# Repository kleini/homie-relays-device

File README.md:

# Relays device for controlling arbitrary loads

## Concept

ESP8266 based controller using Homie and a I/O Extender to control 16 relays. Everything should fit in a DIN Rail Standard Height Module Box.

## Hardware

 * ESP8266 12e module
 * I²C I/O Extender MCP23016 (16 GPIOs)
 * self designed board fitting into DIN Rail Standard Height Module Box (see hardware branch)
 * 230V power supply

I²C device address configured to 0x20.

DCDC converter from 12V down to 3.3V running ESP8266 and MCP23016. Some driver chip will be used to drive the relay coils.

Every output will have its own indicator LED.

### MCP23016

This chip is able to drive a LED directly on the high output.

### Lessons learned

#### PCF8575

The PCF8575 has only a very low continuous output high current of -4mA. This allows possibly to light up a low current LED but not much more. Will drop the use of this chip and use something with higher output high current.

## Case

Everything should fit in a DIN Rail Standard Module Box like the following

The design of the printed circuit board will finally show, how much relays I can fit in which box. Current design goal is to have a 3 module wide box. If I can not fit 16 230V 5A relays switches onto the PCB in this box,
I will take a wider box.

The box can carry up to 3 PCBs. I will use only 2, a large one in the bottom for power supply and relays switches and a smaller one in the top for ESP8266, indicator LEDs and I/O expander.

## Compiling

Software will be based on latest homie-esp8266 development cycle.

Extended/modified libraries are necessary.

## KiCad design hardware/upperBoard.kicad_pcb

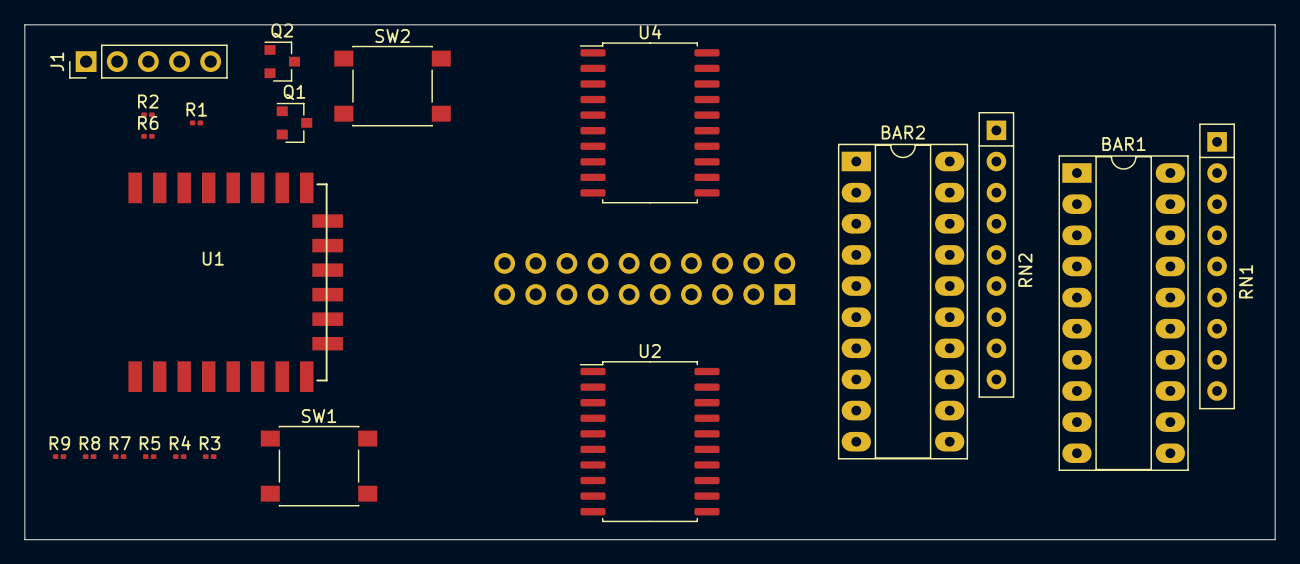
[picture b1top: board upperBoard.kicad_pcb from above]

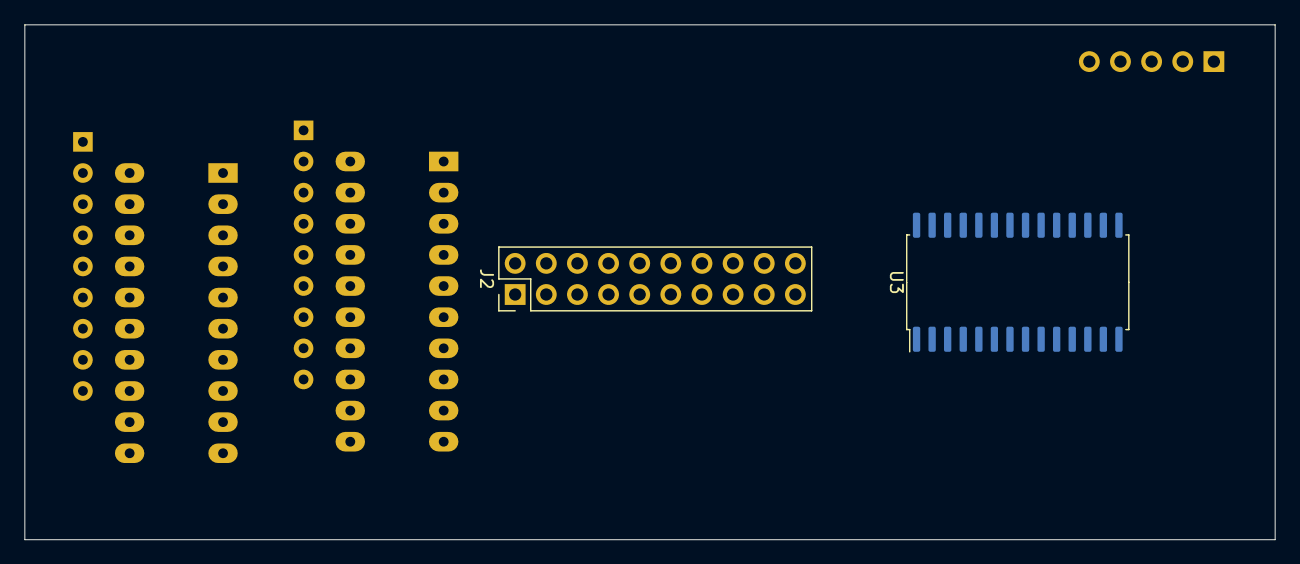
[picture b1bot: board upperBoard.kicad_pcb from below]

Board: 2 copper layers, 102.0 x 42.0 mm, 23 parts (2 on the bottom side), 64 nets, no tracks yet.

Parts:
BAR1, BAR2: HDSP-4830_2; DIP-20_W7.62mm_Socket_LongPads
J1: Program interface; PinHeader_1x05_P2.54mm_Vertical
J2: Conn_02x10_Odd_Even; PinHeader_2x10_P2.54mm_Vertical
Q1, Q2: MMBT3904; SOT-23
R1, R2, R3, R4, R6, R7, R8, R9: 10K; R_0201_0603Metric
R5: 4.7K; R_0201_0603Metric
RN1: 150; R_Array_SIP9
RN2: R_Network08; R_Array_SIP9
SW1: Reset; SW_Push_1P1T_NO_6x6mm_H9.5mm
SW2: Prog; SW_Push_1P1T_NO_6x6mm_H9.5mm
U1: ESP-12F; ESP-12E_SMD
U2, U4: A2982; SOIC-20W_7.5x12.8mm_P1.27mm
U3: MCP23017_SO; SOIC-28W_7.5x17.9mm_P1.27mm

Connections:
/01: J2.15, U2.20
/02: J2.13, U2.19
/03: J2.11, U2.18
/3.3V: J2.17, R1.1, R2.1, R6.1, R7.1, R8.1, R9.1, U1.8, U3.9
/04: J2.9, U2.17
/05: J2.7, U2.16
/06: J2.5, U2.15
/07: J2.3, U2.14
/08: J2.1, U2.13
/09: J2.2, U4.20
/10: J2.4, U4.19
/11: J2.6, U4.18
/12: J2.8, U4.17
/12V: J2.19, U2.9, U4.9
/13: J2.10, U4.16
/14: J2.12, U4.15
/15: J2.14, U4.14
/16: J2.16, U4.13
/DTR: J1.3, Q2.2, R3.1
/GND: J1.5, J2.18, J2.20, R5.2, RN1.1, RN2.1, SW1.1, SW2.2, U1.9, U2.12, U3.10, U3.15, U3.16, U3.17, U4.12
/RTS: J1.4, Q1.2, R4.1
/RXD: J1.1, U1.16
/TXD: J1.2, U1.15
unnamed: BAR1.1, U2.1, U3.21
unnamed: BAR1.2, U2.2, U3.22
unnamed: BAR1.3, U2.3, U3.23
unnamed: BAR1.4, U2.4, U3.24
unnamed: BAR1.5, U2.5, U3.25
unnamed: BAR1.6, U2.6, U3.26
unnamed: BAR1.7, U2.7, U3.27
unnamed: BAR1.8, U2.8, U3.28
unnamed: BAR1.13, RN1.9
unnamed: BAR1.14, RN1.8
unnamed: BAR1.15, RN1.7
unnamed: BAR1.16, RN1.6
unnamed: BAR1.17, RN1.5
unnamed: BAR1.18, RN1.4
unnamed: BAR1.19, RN1.3
unnamed: BAR1.20, RN1.2
unnamed: BAR2.1, U3.1, U4.1
unnamed: BAR2.2, U3.2, U4.2
unnamed: BAR2.3, U3.3, U4.3
unnamed: BAR2.4, U3.4, U4.4
unnamed: BAR2.5, U3.5, U4.5
unnamed: BAR2.6, U3.6, U4.6
unnamed: BAR2.7, U3.7, U4.7
unnamed: BAR2.8, U3.8, U4.8
unnamed: BAR2.13, RN2.9
unnamed: BAR2.14, RN2.8
unnamed: BAR2.15, RN2.7
unnamed: BAR2.16, RN2.6
unnamed: BAR2.17, RN2.5
unnamed: BAR2.18, RN2.4
unnamed: BAR2.19, RN2.3
unnamed: BAR2.20, RN2.2
unnamed: Q1.1, R3.2
unnamed: Q1.3, R1.2, SW1.2, U1.1, U3.18
unnamed: Q2.1, R4.2
unnamed: Q2.3, R6.2, SW2.1, U1.12
unnamed: R2.2, U1.3
unnamed: R5.1, U1.10
unnamed: R7.2, U1.14, U3.12
unnamed: R8.2, U1.13, U3.13
unnamed: R9.2, U1.11

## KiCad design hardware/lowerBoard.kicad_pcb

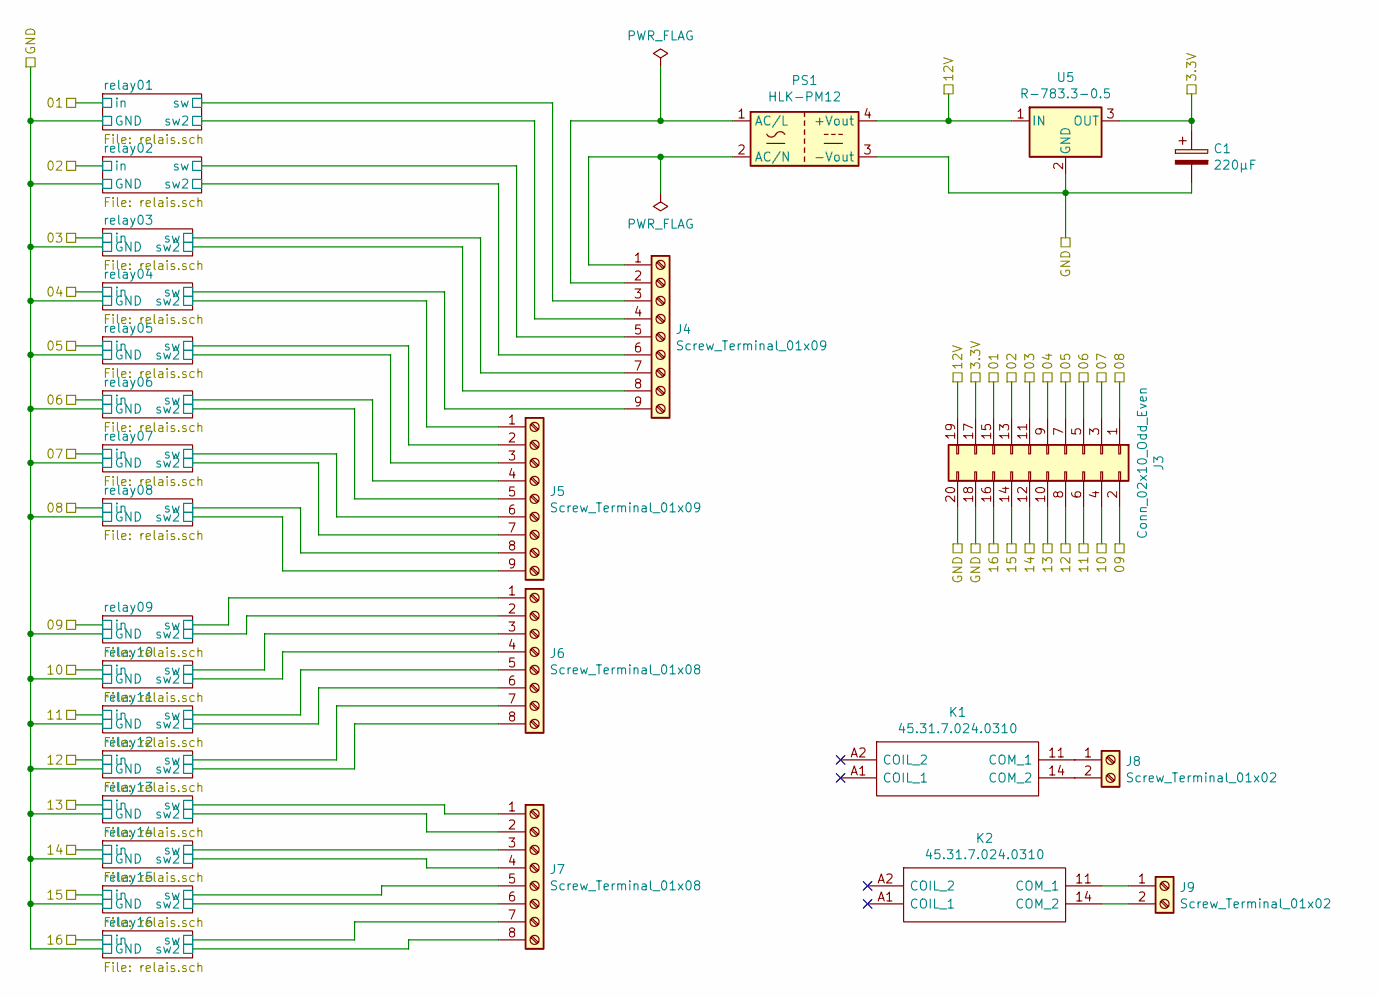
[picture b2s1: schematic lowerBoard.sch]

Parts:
C1: 220µF; CP_Radial_D6.3mm_P2.50mm
J3: Conn_02x10_Odd_Even; PinHeader_2x10_P2.54mm_Vertical
J4, J5: Screw_Terminal_01x09; TerminalBlock_RND_205-00239_1x09_P5.08mm_Horizontal
J6, J7: Screw_Terminal_01x08; TerminalBlock_RND_205-00238_1x08_P5.08mm_Horizontal
J8, J9: Screw_Terminal_01x02; TerminalBlock_MetzConnect_Type101_RT01602HBWC_1x02_P5.08mm_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
K1, K2: 45.31.7.024.0310; finder-45.31.7.024.0310; Manufacturer_Part_Number 45.31.7.024.0310
PS1: HLK-PM12; Converter_ACDC_HiLink_HLK-PMxx
U5: R-783.3-0.5; Converter_DCDC_RECOM_R-78E-0.5_THT

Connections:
/01: J3.15; also elsewhere on the board
/02: J3.13; also elsewhere on the board
/03: J3.11; also elsewhere on the board
/3.3V: C1.1, J3.17, U5.3 (OUT)
/04: J3.9; also elsewhere on the board
/05: J3.7; also elsewhere on the board
/06: J3.5; also elsewhere on the board
/07: J3.3; also elsewhere on the board
/08: J3.1; also elsewhere on the board
/09: J3.2; also elsewhere on the board
/10: J3.4; also elsewhere on the board
/11: J3.6; also elsewhere on the board
/12: J3.8; also elsewhere on the board
/12V: J3.19, PS1.4 (+Vout), U5.1 (IN)
/13: J3.10; also elsewhere on the board
/14: J3.12; also elsewhere on the board
/15: J3.14; also elsewhere on the board
/16: J3.16; also elsewhere on the board
/GND: C1.2, J3.18, J3.20, PS1.3 (-Vout), U5.2 (GND); also elsewhere on the board
/relay01/sw: J4.3; also elsewhere on the board
/relay01/sw2: J4.4; also elsewhere on the board
/relay02/sw: J4.5; also elsewhere on the board
/relay02/sw2: J4.6; also elsewhere on the board
/relay03/sw: J4.7; also elsewhere on the board
/relay03/sw2: J4.8; also elsewhere on the board
/relay04/sw: J4.9; also elsewhere on the board
/relay04/sw2: J5.1; also elsewhere on the board
/relay05/sw: J5.2; also elsewhere on the board
/relay05/sw2: J5.3; also elsewhere on the board
/relay06/sw: J5.4; also elsewhere on the board
/relay06/sw2: J5.5; also elsewhere on the board
/relay07/sw: J5.6; also elsewhere on the board
/relay07/sw2: J5.7; also elsewhere on the board
/relay08/sw: J5.8; also elsewhere on the board
/relay08/sw2: J5.9; also elsewhere on the board
/relay09/sw: J6.1; also elsewhere on the board
/relay09/sw2: J6.2; also elsewhere on the board
/relay10/sw: J6.3; also elsewhere on the board
/relay10/sw2: J6.4; also elsewhere on the board
/relay11/sw: J6.5; also elsewhere on the board
/relay11/sw2: J6.6; also elsewhere on the board
/relay12/sw: J6.7; also elsewhere on the board
/relay12/sw2: J6.8; also elsewhere on the board
/relay13/sw: J7.1; also elsewhere on the board
/relay13/sw2: J7.2; also elsewhere on the board
/relay14/sw: J7.3; also elsewhere on the board
/relay14/sw2: J7.4; also elsewhere on the board
/relay15/sw: J7.5; also elsewhere on the board
/relay15/sw2: J7.6; also elsewhere on the board
/relay16/sw: J7.7; also elsewhere on the board
/relay16/sw2: J7.8; also elsewhere on the board
unnamed: J4.1, PS1.2 (AC/N)
unnamed: J4.2, PS1.1 (AC/L)
unnamed: J8.1, K1.11 (COM_1)
unnamed: J8.2, K1.14 (COM_2)
unnamed: J9.1, K2.11 (COM_1)
unnamed: J9.2, K2.14 (COM_2)

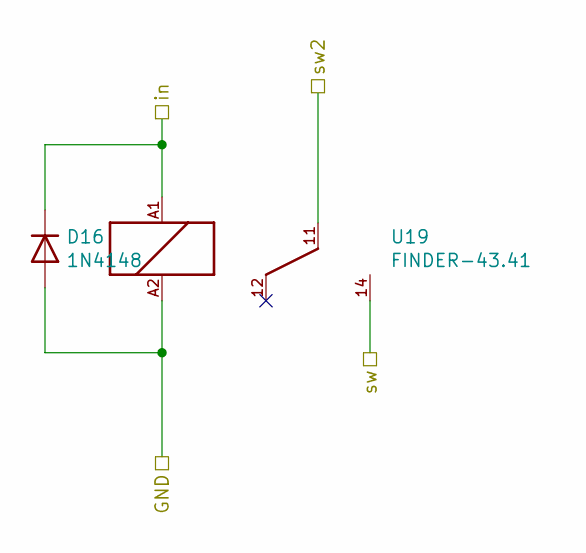
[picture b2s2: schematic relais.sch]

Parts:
D2: 1N4148; D_DO-35_SOD27_P7.62mm_Horizontal
U7: FINDER-43.41; finder-43.41

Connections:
/02: D2.1 (K), U7.A1; also elsewhere on the board
/GND: D2.2 (A), U7.A2; also elsewhere on the board
/relay02/sw: U7.14; also elsewhere on the board
/relay02/sw2: U7.11; also elsewhere on the board

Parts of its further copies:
D1, D3, D4, D5, D6, D7, D8, D9, D10, D11, D12, D13, D14, D15, D16: 1N4148; D_DO-35_SOD27_P7.62mm_Horizontal
U6, U8, U9, U10, U11, U12, U13, U14, U15, U16, U17, U18, U19, U20, U21: FINDER-43.41; finder-43.41

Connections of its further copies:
/01: D1.1 (K), U6.A1; also elsewhere on the board
/03: D3.1 (K), U8.A1; also elsewhere on the board
/04: D4.1 (K), U9.A1; also elsewhere on the board
/05: D5.1 (K), U10.A1; also elsewhere on the board
/06: D6.1 (K), U11.A1; also elsewhere on the board
/07: D7.1 (K), U12.A1; also elsewhere on the board
/08: D8.1 (K), U13.A1; also elsewhere on the board
/09: D9.1 (K), U14.A1; also elsewhere on the board
/10: D10.1 (K), U15.A1; also elsewhere on the board
/11: D11.1 (K), U16.A1; also elsewhere on the board
/12: D12.1 (K), U17.A1; also elsewhere on the board
/13: D13.1 (K), U18.A1; also elsewhere on the board
/14: D16.1 (K), U19.A1; also elsewhere on the board
/15: D14.1 (K), U20.A1; also elsewhere on the board
/16: D15.1 (K), U21.A1; also elsewhere on the board
/GND: D1.2 (A), D3.2 (A), D4.2 (A), D5.2 (A), D6.2 (A), D7.2 (A), D8.2 (A), D9.2 (A), D10.2 (A), D11.2 (A), D12.2 (A), D13.2 (A), D14.2 (A), D15.2 (A), D16.2 (A), U6.A2, U8.A2, U9.A2, U10.A2, U11.A2, U12.A2, U13.A2, U14.A2, U15.A2, U16.A2, U17.A2, U18.A2, U19.A2, U20.A2, U21.A2; also elsewhere on the board
/relay01/sw: U6.14; also elsewhere on the board
/relay01/sw2: U6.11; also elsewhere on the board
/relay03/sw: U8.14; also elsewhere on the board
/relay03/sw2: U8.11; also elsewhere on the board
/relay04/sw: U9.14; also elsewhere on the board
/relay04/sw2: U9.11; also elsewhere on the board
/relay05/sw: U10.14; also elsewhere on the board
/relay05/sw2: U10.11; also elsewhere on the board
/relay06/sw: U11.14; also elsewhere on the board
/relay06/sw2: U11.11; also elsewhere on the board
/relay07/sw: U12.14; also elsewhere on the board
/relay07/sw2: U12.11; also elsewhere on the board
/relay08/sw: U13.14; also elsewhere on the board
/relay08/sw2: U13.11; also elsewhere on the board
/relay09/sw: U14.14; also elsewhere on the board
/relay09/sw2: U14.11; also elsewhere on the board
/relay10/sw: U15.14; also elsewhere on the board
/relay10/sw2: U15.11; also elsewhere on the board
/relay11/sw: U16.14; also elsewhere on the board
/relay11/sw2: U16.11; also elsewhere on the board
/relay12/sw: U17.14; also elsewhere on the board
/relay12/sw2: U17.11; also elsewhere on the board
/relay13/sw: U18.14; also elsewhere on the board
/relay13/sw2: U18.11; also elsewhere on the board
/relay14/sw: U19.14; also elsewhere on the board
/relay14/sw2: U19.11; also elsewhere on the board
/relay15/sw: U20.14; also elsewhere on the board
/relay15/sw2: U20.11; also elsewhere on the board
/relay16/sw: U21.14; also elsewhere on the board
/relay16/sw2: U21.11; also elsewhere on the board

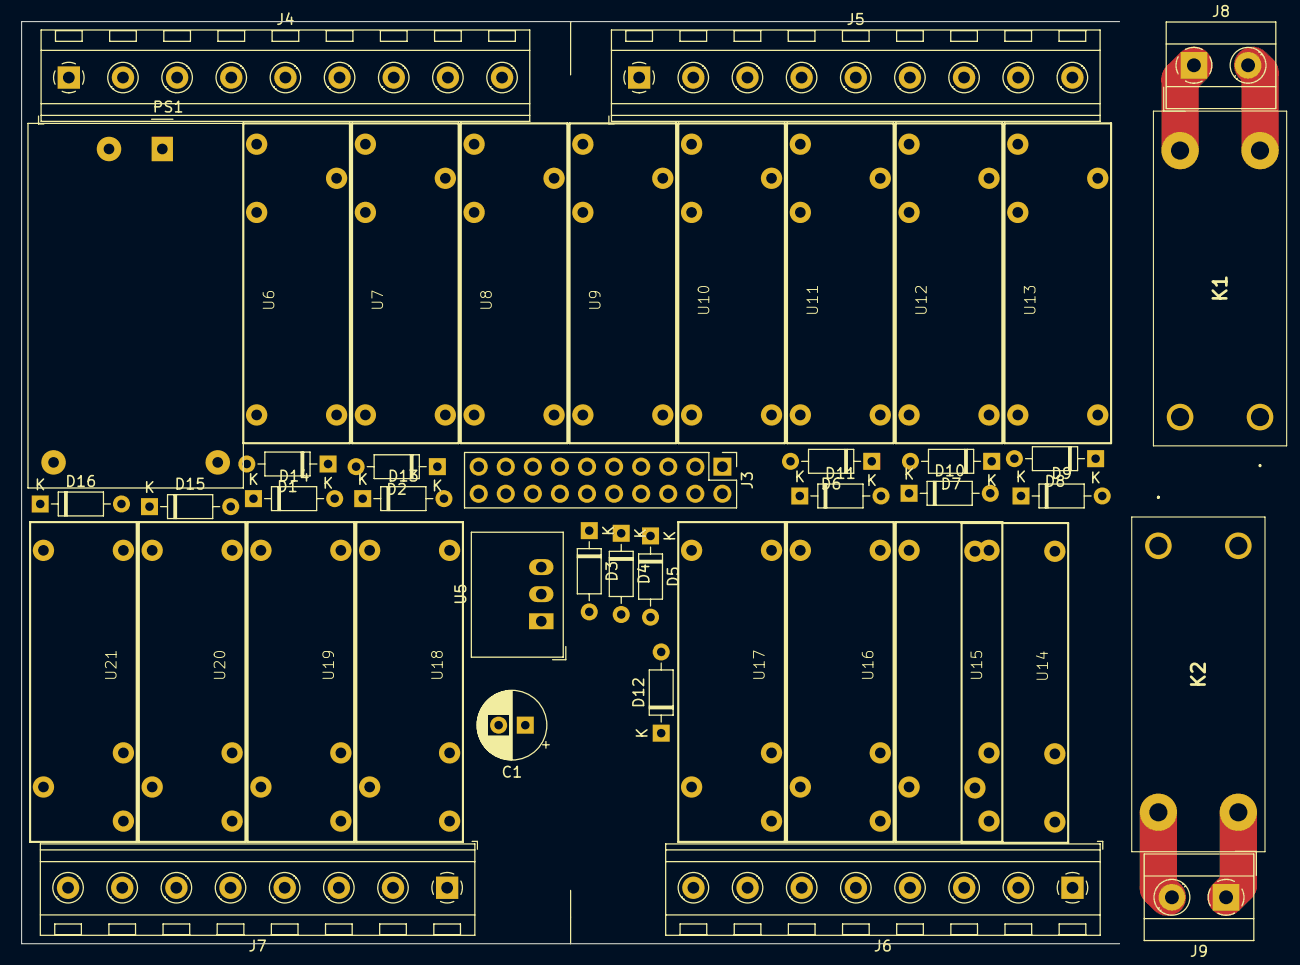
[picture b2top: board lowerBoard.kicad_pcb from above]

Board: 2 copper layers, 103.0 x 86.5 mm, 44 parts (0 on the bottom side), 57 nets.

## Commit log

2019-09-25 first simple description
2019-09-25 added Homie only
2019-09-25 added gitignore
2019-09-26 written down more design decisions
2019-09-26 inline image
2019-09-26 basic Homie device setup
2019-09-26 started to create schematic for hardware
2019-09-27 corrected N channel MOSFET transistor
2019-09-27 added programming interface
2019-09-27 a lot of progress in hardware design
    separated different board into separate hierarchical schematics
    hierarchical schematics for parts to be multiplied
    separate project files for each board for creating separate PCBs without interconnection
2019-09-27 removed useless directory
2019-10-02 started to replace PCF8575 with MCP23016 and separated LEDs with arrays
2019-10-03 correct name relays
2019-10-03 renamed hardware files
2019-10-03 replaced separated driver parts with driver chips and LED bars
2019-10-08 extracted relay to sub schematic to be able to multiply it
2019-10-19 finished schematic mostly
    started to create lower PCB
2020-01-14 upgraded libraries and tested nemidiys fix for not working OTA
2020-02-11 test latest OTA tweaks
2020-12-25 upgrade to homie-esp8266 develop
2020-12-27 add ADC node
    upgrade to fix branch of async-mqtt-client
    upgrade to latest espressif8266
2021-01-11 started to replace MCP23016 with MCP23017
2021-01-11 monitor heap
2021-01-14 replaced MCP23016 with MCP23017
2021-01-14 some settings for KiCad
2021-01-17 feat: add MCP23017 and test it a little bit
2021-01-21 prototype picture
2021-01-21 schematic picture
2021-01-21 lower board fixes and started with upper printed circuit board
2021-01-27 continue to design lower pcb
2021-01-29 move on to 16A relays
2021-02-09 develop branch of async-mqtt-client works great
2021-02-11 use littlefs
